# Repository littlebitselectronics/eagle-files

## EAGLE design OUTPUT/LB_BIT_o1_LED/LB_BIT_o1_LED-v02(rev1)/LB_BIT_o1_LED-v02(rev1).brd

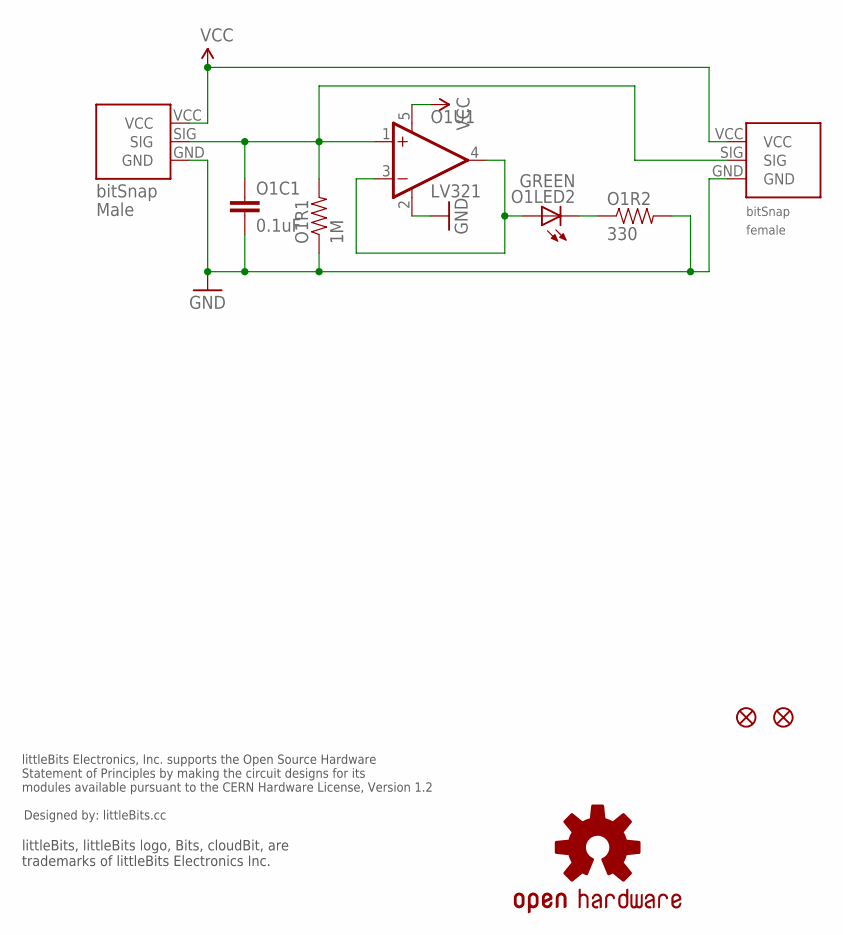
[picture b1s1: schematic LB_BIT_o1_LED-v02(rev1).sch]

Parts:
JP1, JP2: FIDUCIAL1X2.5; FIDUCIAL-1X2.5
O1BSF: BITSNAP_FEMALE
O1BSM: BITSNAP_MALE
O1C1: 0.1uF; 0603-CAP
O1LED2: GREEN; LED-1206
O1R1: 1M; 0603-RES
O1R2: 330; 0603-RES
O1U1: LV321; SC70-5
U$1: OSHWCREDIT
U$3: OSHW-LOGOL; OSHW-LOGO-L

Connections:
GND: O1BSF.GND, O1BSM.GND, O1C1.2, O1R1.1, O1R2.2, O1U1.2 (V-)
LEDGND: O1LED2.C, O1R2.1
unnamed: O1LED2.A, O1U1.3 (-IN), O1U1.4 (OUT)
SIG: O1BSF.SIG, O1BSM.SIG, O1C1.1, O1R1.2, O1U1.1 (+IN)
VCC: O1BSF.VCC, O1BSM.VCC, O1U1.5 (V+)

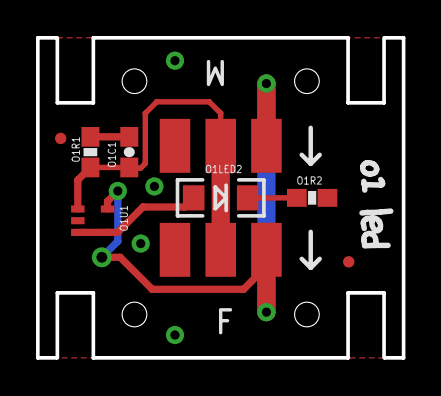
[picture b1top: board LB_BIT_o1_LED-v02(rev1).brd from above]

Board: 2 copper layers, 20.3 x 17.8 mm, 12 parts (0 on the bottom side), 5 nets.

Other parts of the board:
U$2: OSHW_FILLX150_NOTEXT

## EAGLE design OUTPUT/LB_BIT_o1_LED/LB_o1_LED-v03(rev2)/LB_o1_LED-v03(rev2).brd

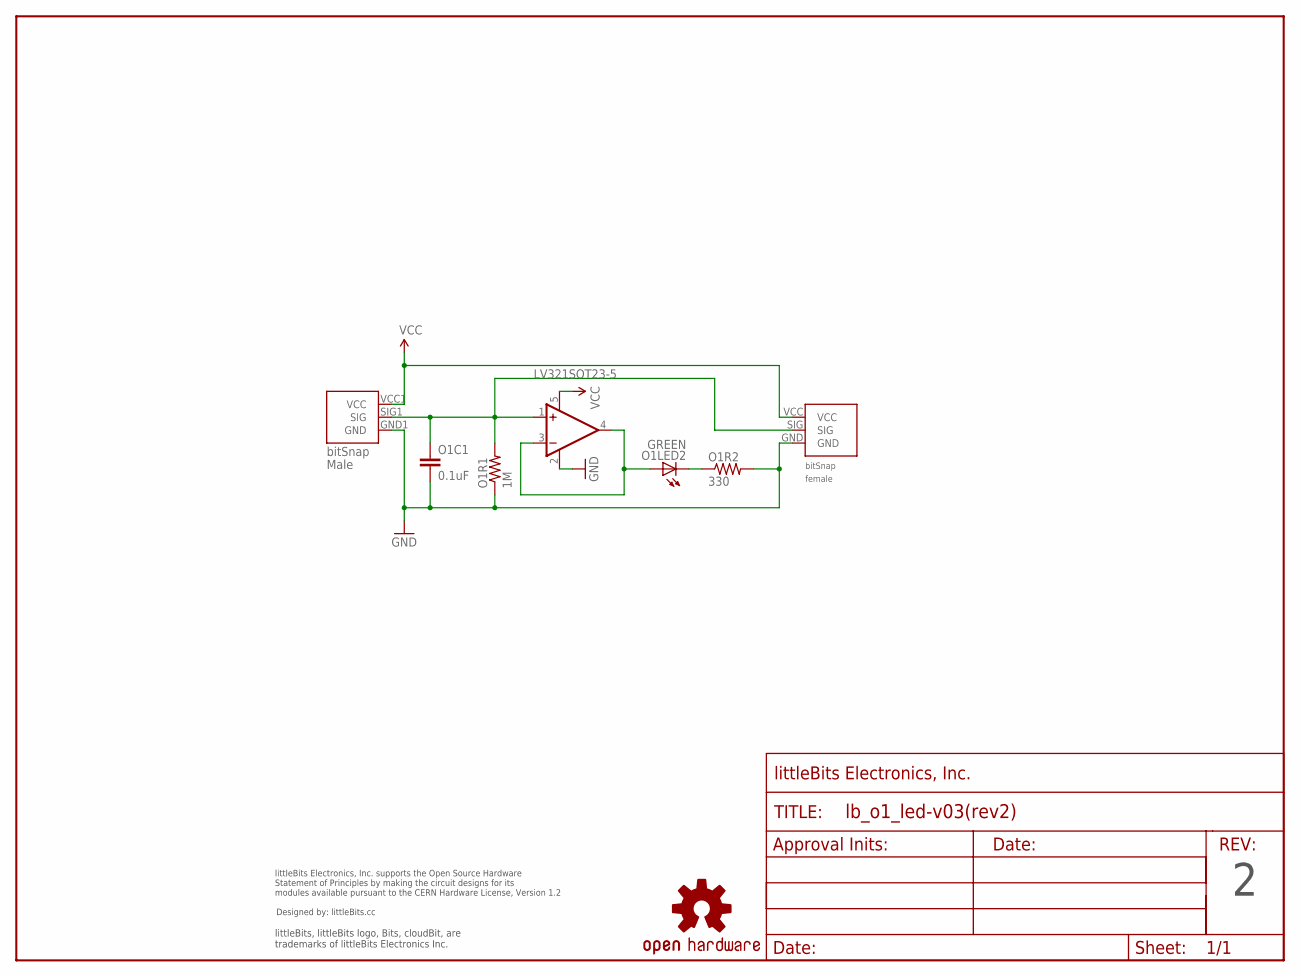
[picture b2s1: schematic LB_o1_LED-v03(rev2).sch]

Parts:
O1BSF: BITSNAP_V03_FEMALE
O1BSM: BITSNAP_V03_MALE
O1C1: 0.1uF; 0603-CAP
O1LED2: GREEN; LED-1206
O1R1: 1M; 0603-RES
O1R2: 330; 0603-RES
O1U1: LV321SOT23-5; SOT23-5
U$1: OSHWCREDIT
U$3: OSHW-LOGOL; OSHW-LOGO-L
U$4: FRAME-LETTER-OHWOHW; FABDWG01-OHW

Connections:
GND: O1BSF.GND, O1BSM.GND1 (GND), O1C1.2, O1R1.1, O1R2.2, O1U1.2 (V-)
LEDGND: O1LED2.C, O1R2.1
unnamed: O1LED2.A, O1U1.3 (-IN), O1U1.4 (OUT)
SIG: O1BSF.SIG, O1BSM.SIG1 (SIG), O1C1.1, O1R1.2, O1U1.1 (+IN)
VCC: O1BSF.VCC, O1BSM.VCC1 (VCC), O1U1.5 (V+)

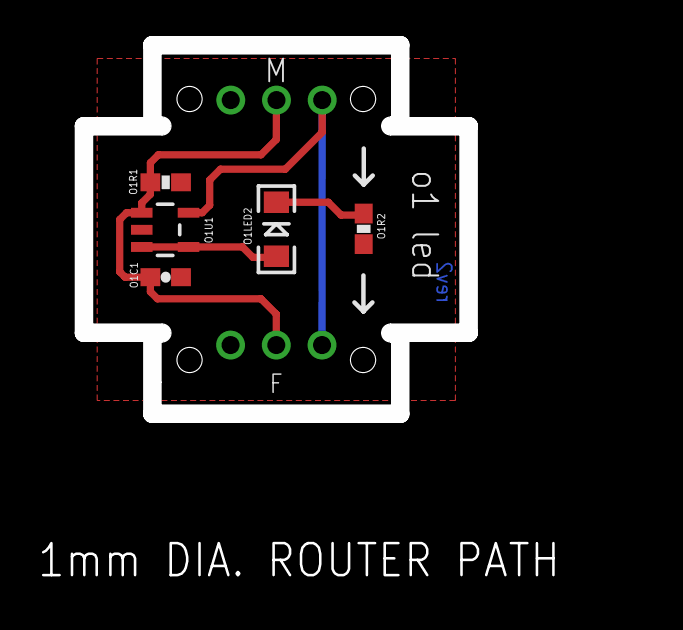
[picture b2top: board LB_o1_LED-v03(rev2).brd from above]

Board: 2 copper layers, 21.4 x 20.5 mm, 11 parts (0 on the bottom side), 5 nets.

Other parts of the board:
U$2: OSHW_FILLX150_NOTEXT

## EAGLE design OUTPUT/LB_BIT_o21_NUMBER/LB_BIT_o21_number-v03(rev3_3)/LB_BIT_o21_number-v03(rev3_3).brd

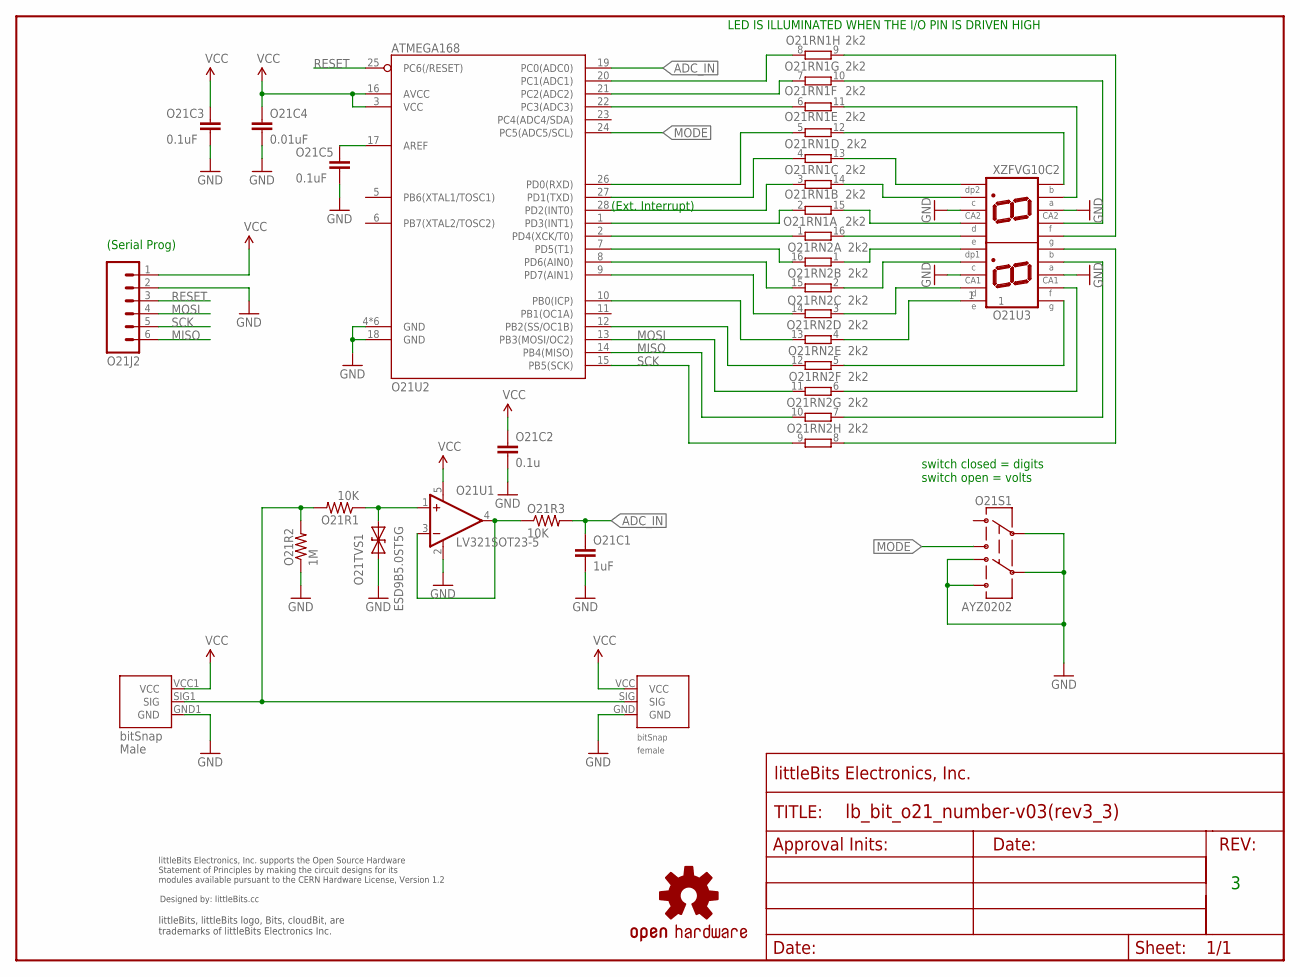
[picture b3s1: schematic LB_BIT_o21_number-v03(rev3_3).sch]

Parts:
O21BSF1: BITSNAP_V03_FEMALE
O21BSM1: BITSNAP_V03_MALE
O21C1: 1uF; CAP-0603
O21C2: 0.1u; CAP-0603
O21C3, O21C5: 0.1uF; CAP-0603
O21C4: 0.01uF; CAP-0603
O21J2: HRD-60.1INCH_NO_SILKSCREEN; SIP6-SM-0.1IN-NOS.S.
O21R1, O21R3: 10K; RES-0603
O21R2: 1M; RES-0603
O21RN1, O21RN2: 2k2; EXB2HV
O21S1: AYZ0202
O21TVS1: ESD9B5.0ST5G; SOD-923
O21U1: LV321SOT23-5; SOT23-5
O21U2: ATMEGA168; VQFN28
O21U3: XZFVG10C2; LED-DUAL7SEG-SM
U$7: OSHWCREDIT
U$16: FRAME-LETTER-OHWOHW; FABDWG01-OHW
U$27: OSHW-LOGOL; OSHW-LOGO-L

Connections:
ADC_IN: O21C1.1, O21R3.2, O21U2.19 (PC0(ADC0))
BIT_SIG: O21R3.1, O21U1.3 (-IN), O21U1.4 (OUT)
GND: O21BSF1.GND, O21BSM1.GND1 (GND), O21C1.2, O21C2.2, O21C3.2, O21C4.2, O21C5.2, O21J2.2, O21R2.1, O21S1.2, O21S1.4, O21S1.5, O21S1.6, O21TVS1.1 (A), O21U1.2 (V-), O21U2.4 (GND), O21U2.18 (GND), O21U2.TH (GND), O21U2.TH@1 (GND), O21U2.TH@2 (GND), O21U2.TH@3 (GND), O21U2.TH@4 (GND), O21U3.3, O21U3.8, O21U3.13, O21U3.18
MISO: O21J2.6, O21RN2.10 (2), O21U2.14 (PB4(MISO))
MODE: O21S1.3, O21U2.24 (PC5(ADC5/SCL))
MOSI: O21J2.4, O21RN2.11 (2), O21U2.13 (PB3(MOSI/OC2))
unnamed: O21RN1.7 (1), O21U2.21 (PC2(ADC2))
unnamed: O21RN1.8 (1), O21U2.20 (PC1(ADC1))
unnamed: O21RN1.6 (1), O21U2.22 (PC3(ADC3))
unnamed: O21RN1.1, O21U2.2 (PD4(XCK/T0))
unnamed: O21RN1.2 (1), O21U2.1 (PD3(INT1))
unnamed: O21RN1.3 (1), O21U2.28 (PD2(INT0))
unnamed: O21RN1.4 (1), O21U2.27 (PD1(TXD))
unnamed: O21RN1.5 (1), O21U2.26 (PD0(RXD))
unnamed: O21RN2.16 (2), O21U2.7 (PD5(T1))
unnamed: O21RN2.15 (2), O21U2.8 (PD6(AIN0))
unnamed: O21RN2.14 (2), O21U2.9 (PD7(AIN1))
unnamed: O21RN2.13 (2), O21U2.10 (PB0(ICP))
unnamed: O21RN2.12 (2), O21U2.12 (PB2(SS/OC1B))
unnamed: O21RN1.16 (2), O21U3.6
unnamed: O21RN1.12 (2), O21U3.11
unnamed: O21RN1.11 (2), O21U3.12
unnamed: O21RN1.10 (2), O21U3.14
unnamed: O21RN1.9 (2), O21U3.15
unnamed: O21RN1.13 (2), O21U3.10
unnamed: O21RN1.15 (2), O21U3.7
unnamed: O21RN1.14 (2), O21U3.9
unnamed: O21RN2.1, O21U3.5
unnamed: O21RN2.2 (1), O21U3.4
unnamed: O21RN2.3 (1), O21U3.2
unnamed: O21RN2.4 (1), O21U3.1
unnamed: O21RN2.5 (1), O21U3.20
unnamed: O21RN2.6 (1), O21U3.19
unnamed: O21RN2.7 (1), O21U3.17
unnamed: O21RN2.8 (1), O21U3.16
unnamed: O21C5.1, O21U2.17 (AREF)
unnamed: O21R1.1, O21TVS1.2 (C), O21U1.1 (+IN)
RESET: O21J2.3, O21U2.25 (PC6(/RESET))
SCK: O21J2.5, O21RN2.9 (2), O21U2.15 (PB5(SCK))
SIG: O21BSF1.SIG, O21BSM1.SIG1 (SIG), O21R1.2, O21R2.2
VCC: O21BSF1.VCC, O21BSM1.VCC1 (VCC), O21C2.1, O21C3.1, O21C4.1, O21J2.1, O21U1.5 (V+), O21U2.3 (VCC), O21U2.16 (AVCC)

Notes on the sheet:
(Ext. Interrupt)
(Serial Prog)
LED IS ILLUMINATED WHEN THE I/O PIN IS DRIVEN HIGH
switch closed = digits switch open = volts

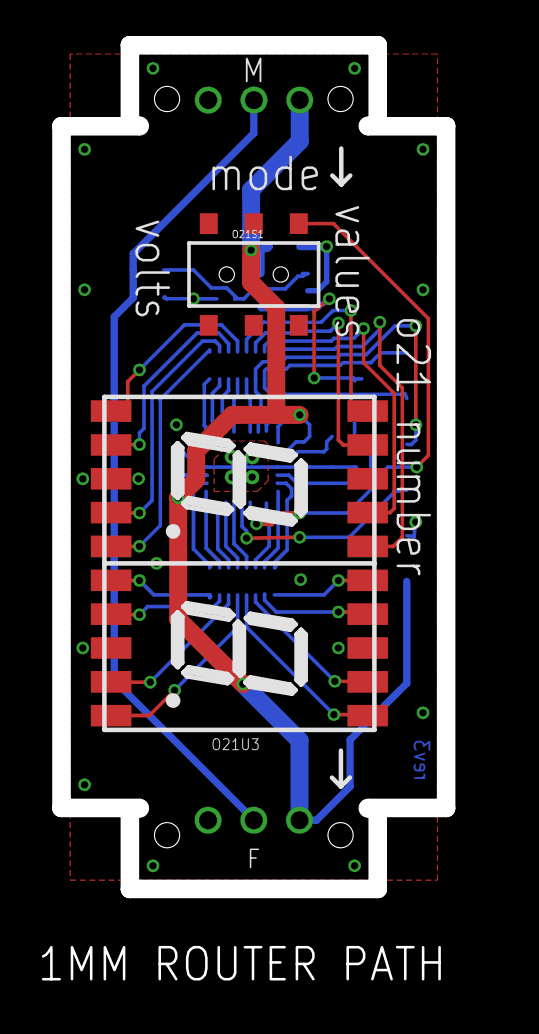
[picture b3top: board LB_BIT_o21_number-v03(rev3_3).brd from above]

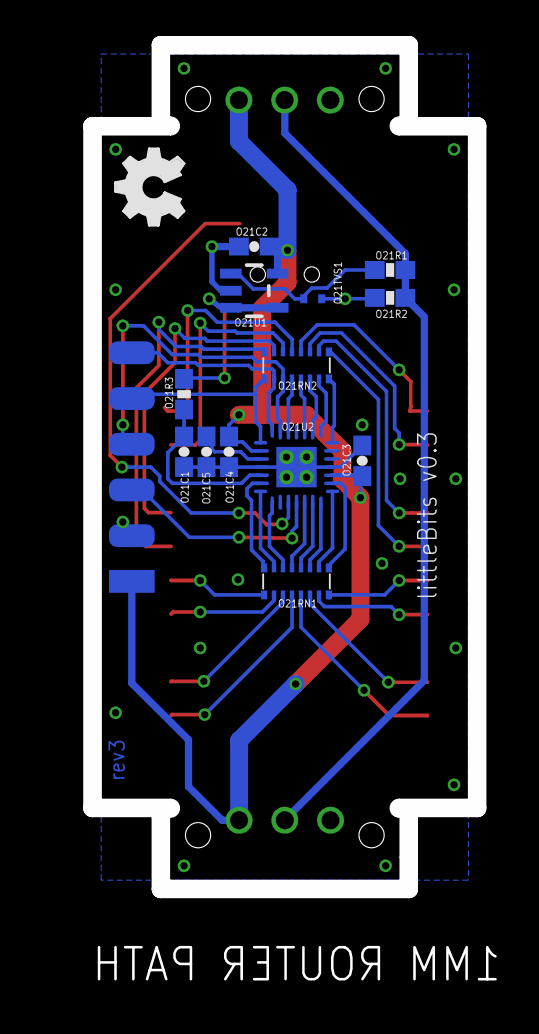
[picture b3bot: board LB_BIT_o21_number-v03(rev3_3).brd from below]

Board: 2 copper layers, 21.4 x 46.9 mm, 22 parts (14 on the bottom side), 41 nets.

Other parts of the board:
U$20: OSHW_FILLX150_NOTEXT

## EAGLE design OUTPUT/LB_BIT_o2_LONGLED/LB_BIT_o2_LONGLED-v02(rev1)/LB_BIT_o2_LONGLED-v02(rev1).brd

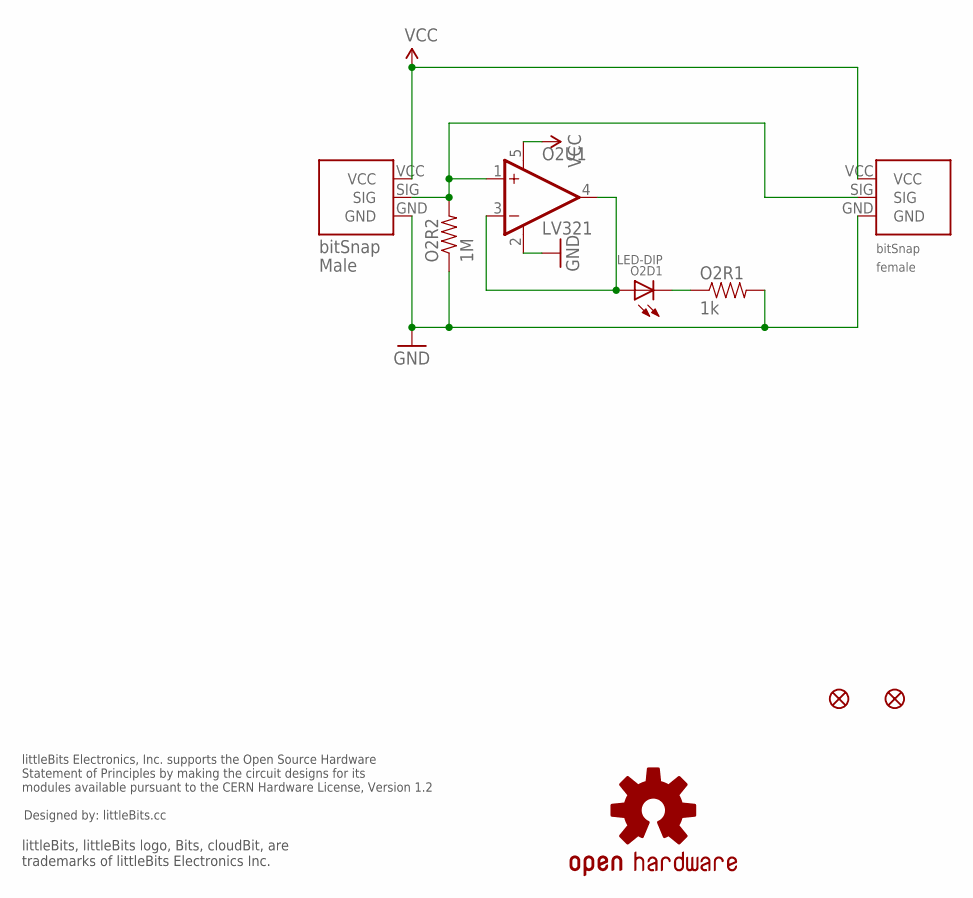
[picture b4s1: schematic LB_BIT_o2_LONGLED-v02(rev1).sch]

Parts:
O2BSF: BITSNAP_FEMALE
O2BSM: BITSNAP_MALE
O2D1: LED-DIP
O2FD1, O2FD2: FIDUCIAL1X2; FIDUCIAL-1X2
O2R1: 1k; 0603-RES
O2R2: 1M; 0603-RES
O2U1: LV321; SC70-5
U$5: OSHWCREDIT
U$14: OSHW-LOGOL; OSHW-LOGO-L

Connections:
GND: O2BSF.GND, O2BSM.GND, O2R1.2, O2R2.1, O2U1.2 (V-)
unnamed: O2D1.C, O2R1.1
unnamed: O2BSF.SIG, O2BSM.SIG, O2R2.2, O2U1.1 (+IN)
unnamed: O2D1.A, O2U1.3 (-IN), O2U1.4 (OUT)
VCC: O2BSF.VCC, O2BSM.VCC, O2U1.5 (V+)

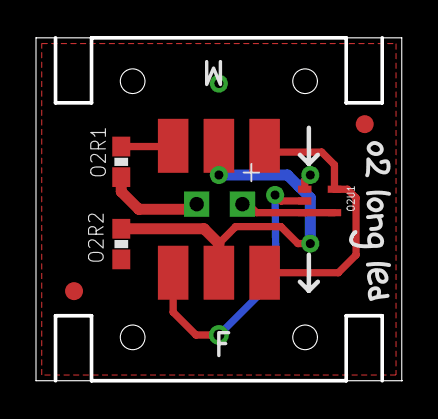
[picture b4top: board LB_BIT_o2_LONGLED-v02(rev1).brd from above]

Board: 2 copper layers, 20.3 x 19.1 mm, 20 parts (0 on the bottom side), 5 nets.

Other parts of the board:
U$1, U$4: O
U$2: 2
U$3, U$11: L
U$7: OSHW_FILLX150_NOTEXT
U$9: N
U$10: G
U$12: E
U$13: D

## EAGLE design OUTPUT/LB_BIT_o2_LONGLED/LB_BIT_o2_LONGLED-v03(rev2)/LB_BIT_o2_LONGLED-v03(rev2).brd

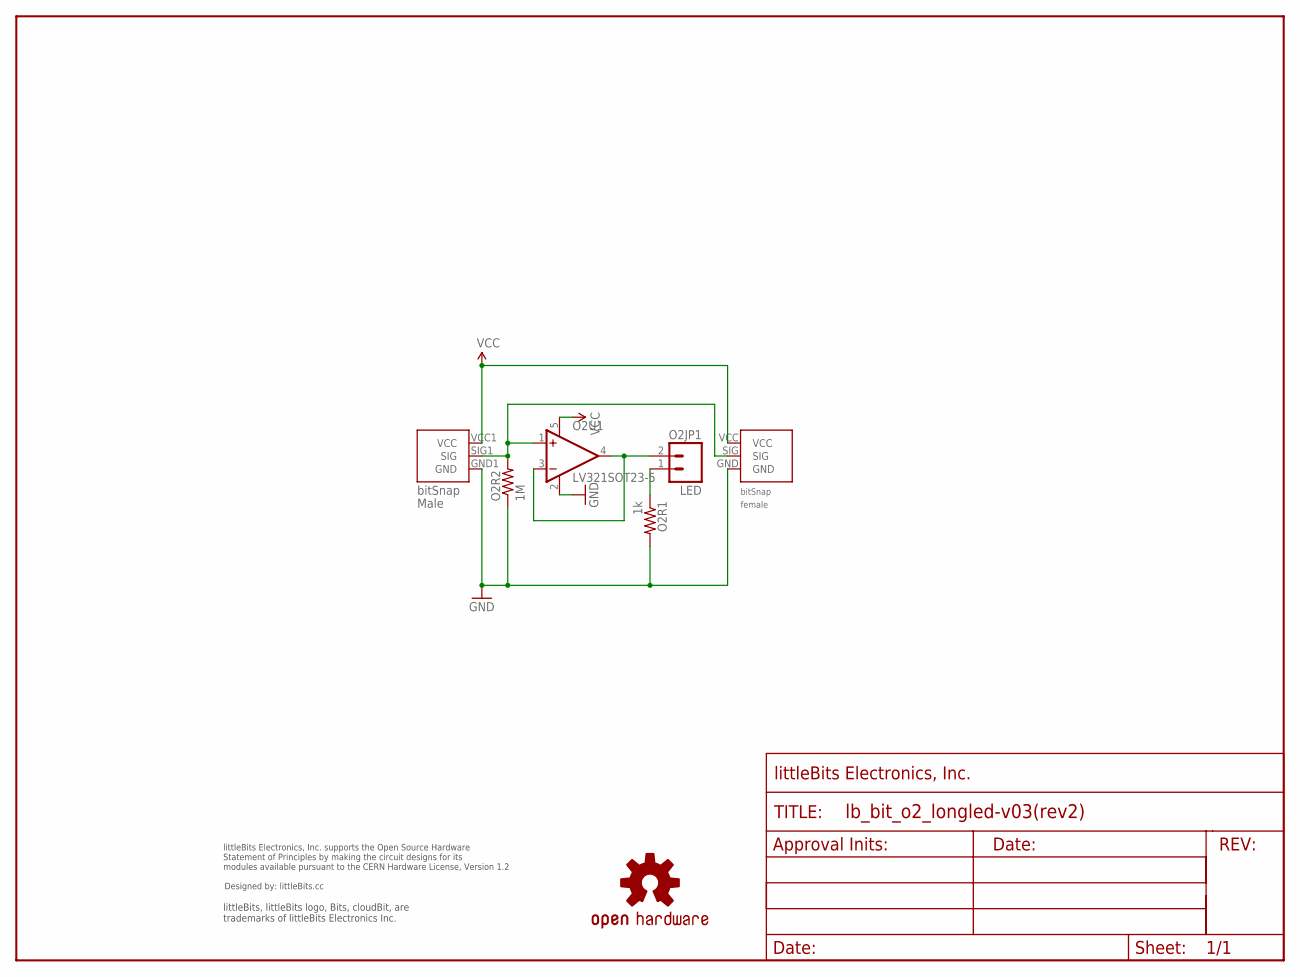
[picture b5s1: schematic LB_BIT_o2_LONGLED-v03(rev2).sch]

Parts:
O2BSF: BITSNAP_V03_FEMALE
O2BSM: BITSNAP_V03_MALE
O2JP1: LED; S2B-PH
O2R1: 1k; 0603-RES
O2R2: 1M; 0603-RES
O2U1: LV321SOT23-5; SOT23-5
U$1: OSHWCREDIT
U$2: FRAME-LETTER-OHWOHW; FABDWG01-OHW
U$14: OSHW-LOGOL; OSHW-LOGO-L

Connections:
GND: O2BSF.GND, O2BSM.GND1 (GND), O2R1.2, O2R2.1, O2U1.2 (V-)
unnamed: O2JP1.1, O2R1.1
unnamed: O2BSF.SIG, O2BSM.SIG1 (SIG), O2R2.2, O2U1.1 (+IN)
unnamed: O2JP1.2, O2U1.3 (-IN), O2U1.4 (OUT)
VCC: O2BSF.VCC, O2BSM.VCC1 (VCC), O2U1.5 (V+)

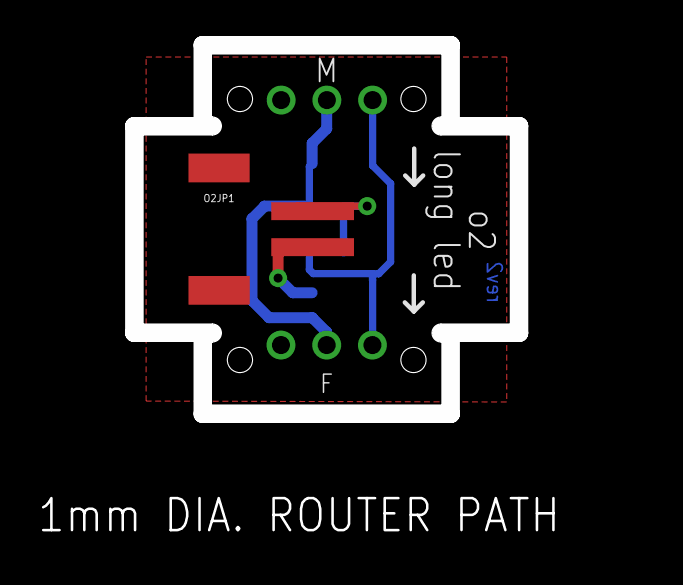
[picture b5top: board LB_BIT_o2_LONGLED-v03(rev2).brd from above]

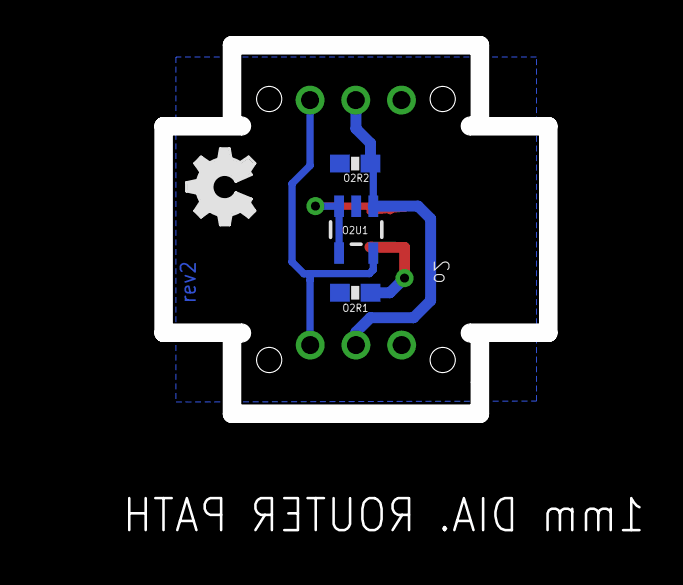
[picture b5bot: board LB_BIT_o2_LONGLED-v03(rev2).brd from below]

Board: 2 copper layers, 21.4 x 20.5 mm, 10 parts (3 on the bottom side), 5 nets.

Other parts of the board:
U$7: OSHW_FILLX150_NOTEXT

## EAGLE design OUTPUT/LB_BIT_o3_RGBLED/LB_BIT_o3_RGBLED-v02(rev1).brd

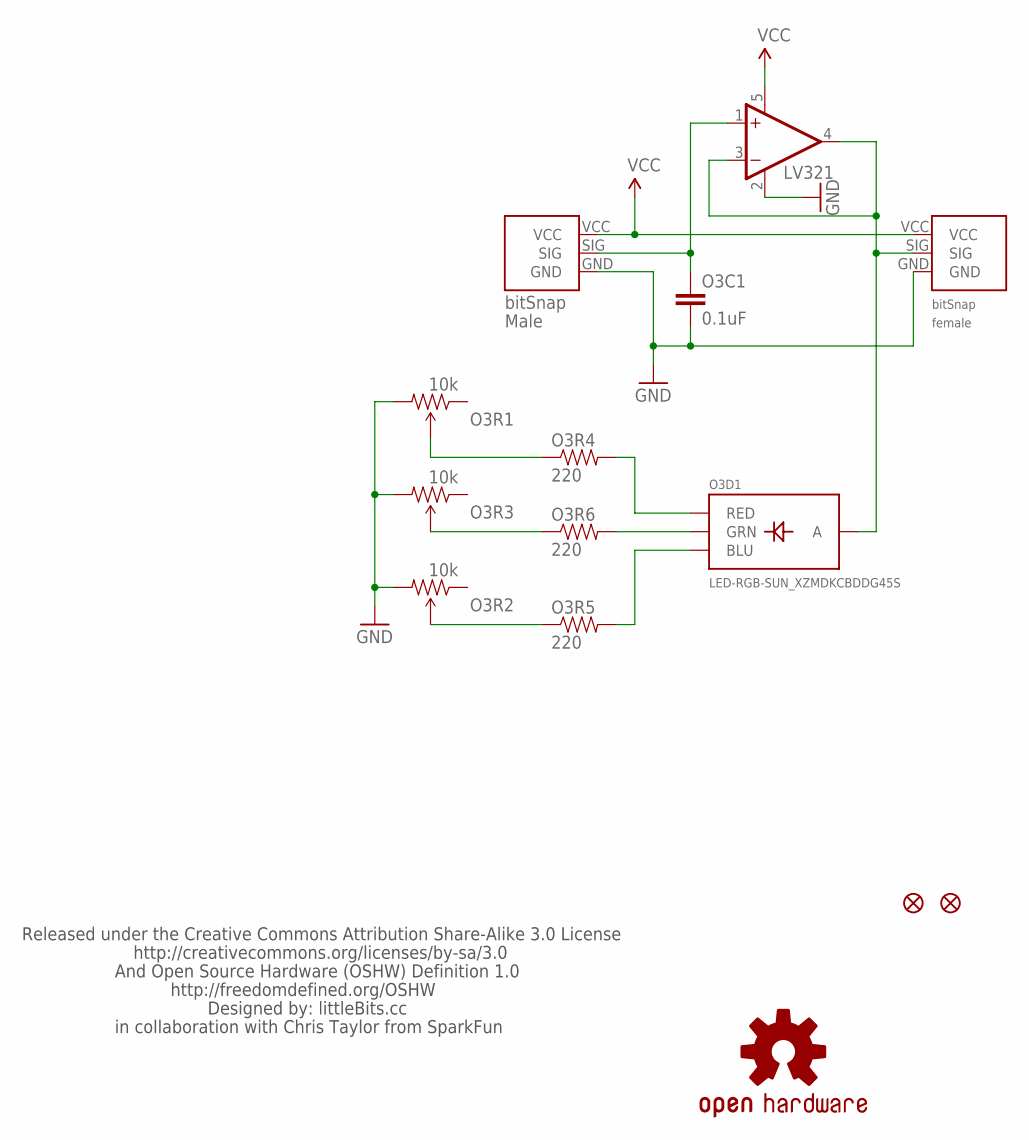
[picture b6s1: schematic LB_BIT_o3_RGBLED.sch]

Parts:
JP1, JP2: FIDUCIAL1X2.5; FIDUCIAL-1X2.5
O3BSF: BITSNAP_FEMALE
O3BSM: BITSNAP_MALE
O3C1: 0.1uF; 0603-CAP
O3D1: LED-RGB-SUN_XZMDKCBDDG45S
O3R1, O3R2, O3R3: 10k; TRIMPOT-3MM
O3R4, O3R5, O3R6: 220; 0603-RES
O3U1: LV321; SC70
U$1: LB_CREDITS; OSHWCREDIT
U$5: OSHW-LOGOL; OSHW-LOGO-L

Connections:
GND: O3BSF.GND, O3BSM.GND, O3C1.2, O3R1.3 (CW), O3R2.3 (CW), O3R3.3 (CW), O3U1.2 (V-)
LED: O3BSF.SIG, O3D1.2 (A), O3U1.3 (-IN), O3U1.4 (OUT)
unnamed: O3R1.2 (WIPER), O3R4.1
unnamed: O3D1.1 (RED), O3R4.2
unnamed: O3D1.4 (GRN), O3R6.2
unnamed: O3D1.3 (BLU), O3R5.2
unnamed: O3R2.2 (WIPER), O3R5.1
unnamed: O3R3.2 (WIPER), O3R6.1
SIG: O3BSM.SIG, O3C1.1, O3U1.1 (+IN)
VCC: O3BSF.VCC, O3BSM.VCC, O3U1.5 (V+)

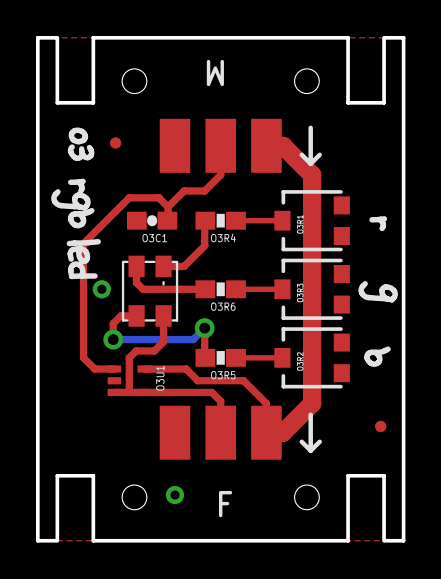
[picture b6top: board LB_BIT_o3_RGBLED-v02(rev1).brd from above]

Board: 2 copper layers, 20.3 x 27.9 mm, 17 parts (0 on the bottom side), 10 nets.

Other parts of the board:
U$2: LB_V02
U$6: OSHW_FILLX150_NOTEXT

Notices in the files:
parts and their libraries:
LITTLEBITS: Released under the Creative Commons Attribution Share-Alike 3.0 License
LITTLEBITS: http://creativecommons.org/license/by-sa/3.0
LITTLEBITS: http://creativecommons.org/licenses/by-sa/3.0
LITTLEBITS: modules available pursuant to the CERN Hardware License,
Version 1.2
